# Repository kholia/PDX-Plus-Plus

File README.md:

#### PDX++ (PDX Plus Plus)

A port of https://github.com/WB2CBA/ADX/ to Raspberry Pi Pico with a couple of
enhancements.

PDX++ uses CD2003 (an AM receiver chip) for RX. For TX, we rely on the
AFSK-driving-Si5351 technique. PDX++ uses the common 3 x BS170 Class-E
amplifier design.

Bands covered: 80-meter to 10-meter.

Note: This repository contains the complete source-code for PDX++ (including
KiCad design files).

Update (17-November-2021): PCB V0.01 was sucessfully validated and is on air!

First QSO from PDX++:

QSOs from PDX++:

Note: This project was built using the following:

- KiCad 6.0.x

- https://github.com/earlephilhower/arduino-pico (v2.6.3)

Cost to build: < 1600 INR (around ~20 USD). Including all connectors + LPF.

RX power consumption is 45mA @ 12.0 volts (around 0.56 watt).

#### Schematic

See [the PDX++ schematic](./PDX++.pdf).

#### Build Tips

For the `PCB V0.01` board, build and test the TX section first.

#### Features

- Easy inbuilt and self-sufficient Si5351 calibration

- Inbuilt BCI (broadcast interference) filter

- New AFSK circuit using a LM393 comparator

- Full CAT support (which avoids VOX mode which can trigger false TX under many
  conditions)

- [Optional] Native FT8 decoding on the Pico (via AA1GD)

  - Use https://github.com/kholia/pico_ft8_xcvr firmware

- [Optional] Native spotting (reporting to PSKReporter.info) when using Pico W

  - https://github.com/kholia/SunshineFT8/

#### BOM Sources

International users can buy from Mouser and DigiKey.

Here are some local BOM sources I use:

- https://inkocean.in/ - CD2003 (Chinese clone which is known to work fine)

- https://rarecomponents.com/store/1002 - NXP 1N4148

- https://projectpoint.in/ - CDIL 7805, PJ307 Stereo Socket, winding wire, high quality passives

- https://www.evelta.com/l7805-positive-voltage-regulator-1-5a-5v/ (alternate)

- https://robu.in/product/si5351a-i2c-8-khz-160-mhz-clock-generator-breakout-board-module/

- https://robu.in/product/raspberry-pi-pico/

- https://www.semikart.com/ - has everything we need and more

#### Credits

- https://github.com/WB2CBA/ADX/

- https://github.com/lu7did/ADX-rp2040

- https://github.com/lu7did (ZCD code, freqPIO code)

- https://github.com/aa1gd/pico_ft8_xcvr (AA1GD, for native FT8 decoding)

- https://www.qrz.com/DB/VU2BGS (layout and general help)

#### References

- https://f5npv.wordpress.com/homebrew-ft8qrp-afp-fsk-trx/

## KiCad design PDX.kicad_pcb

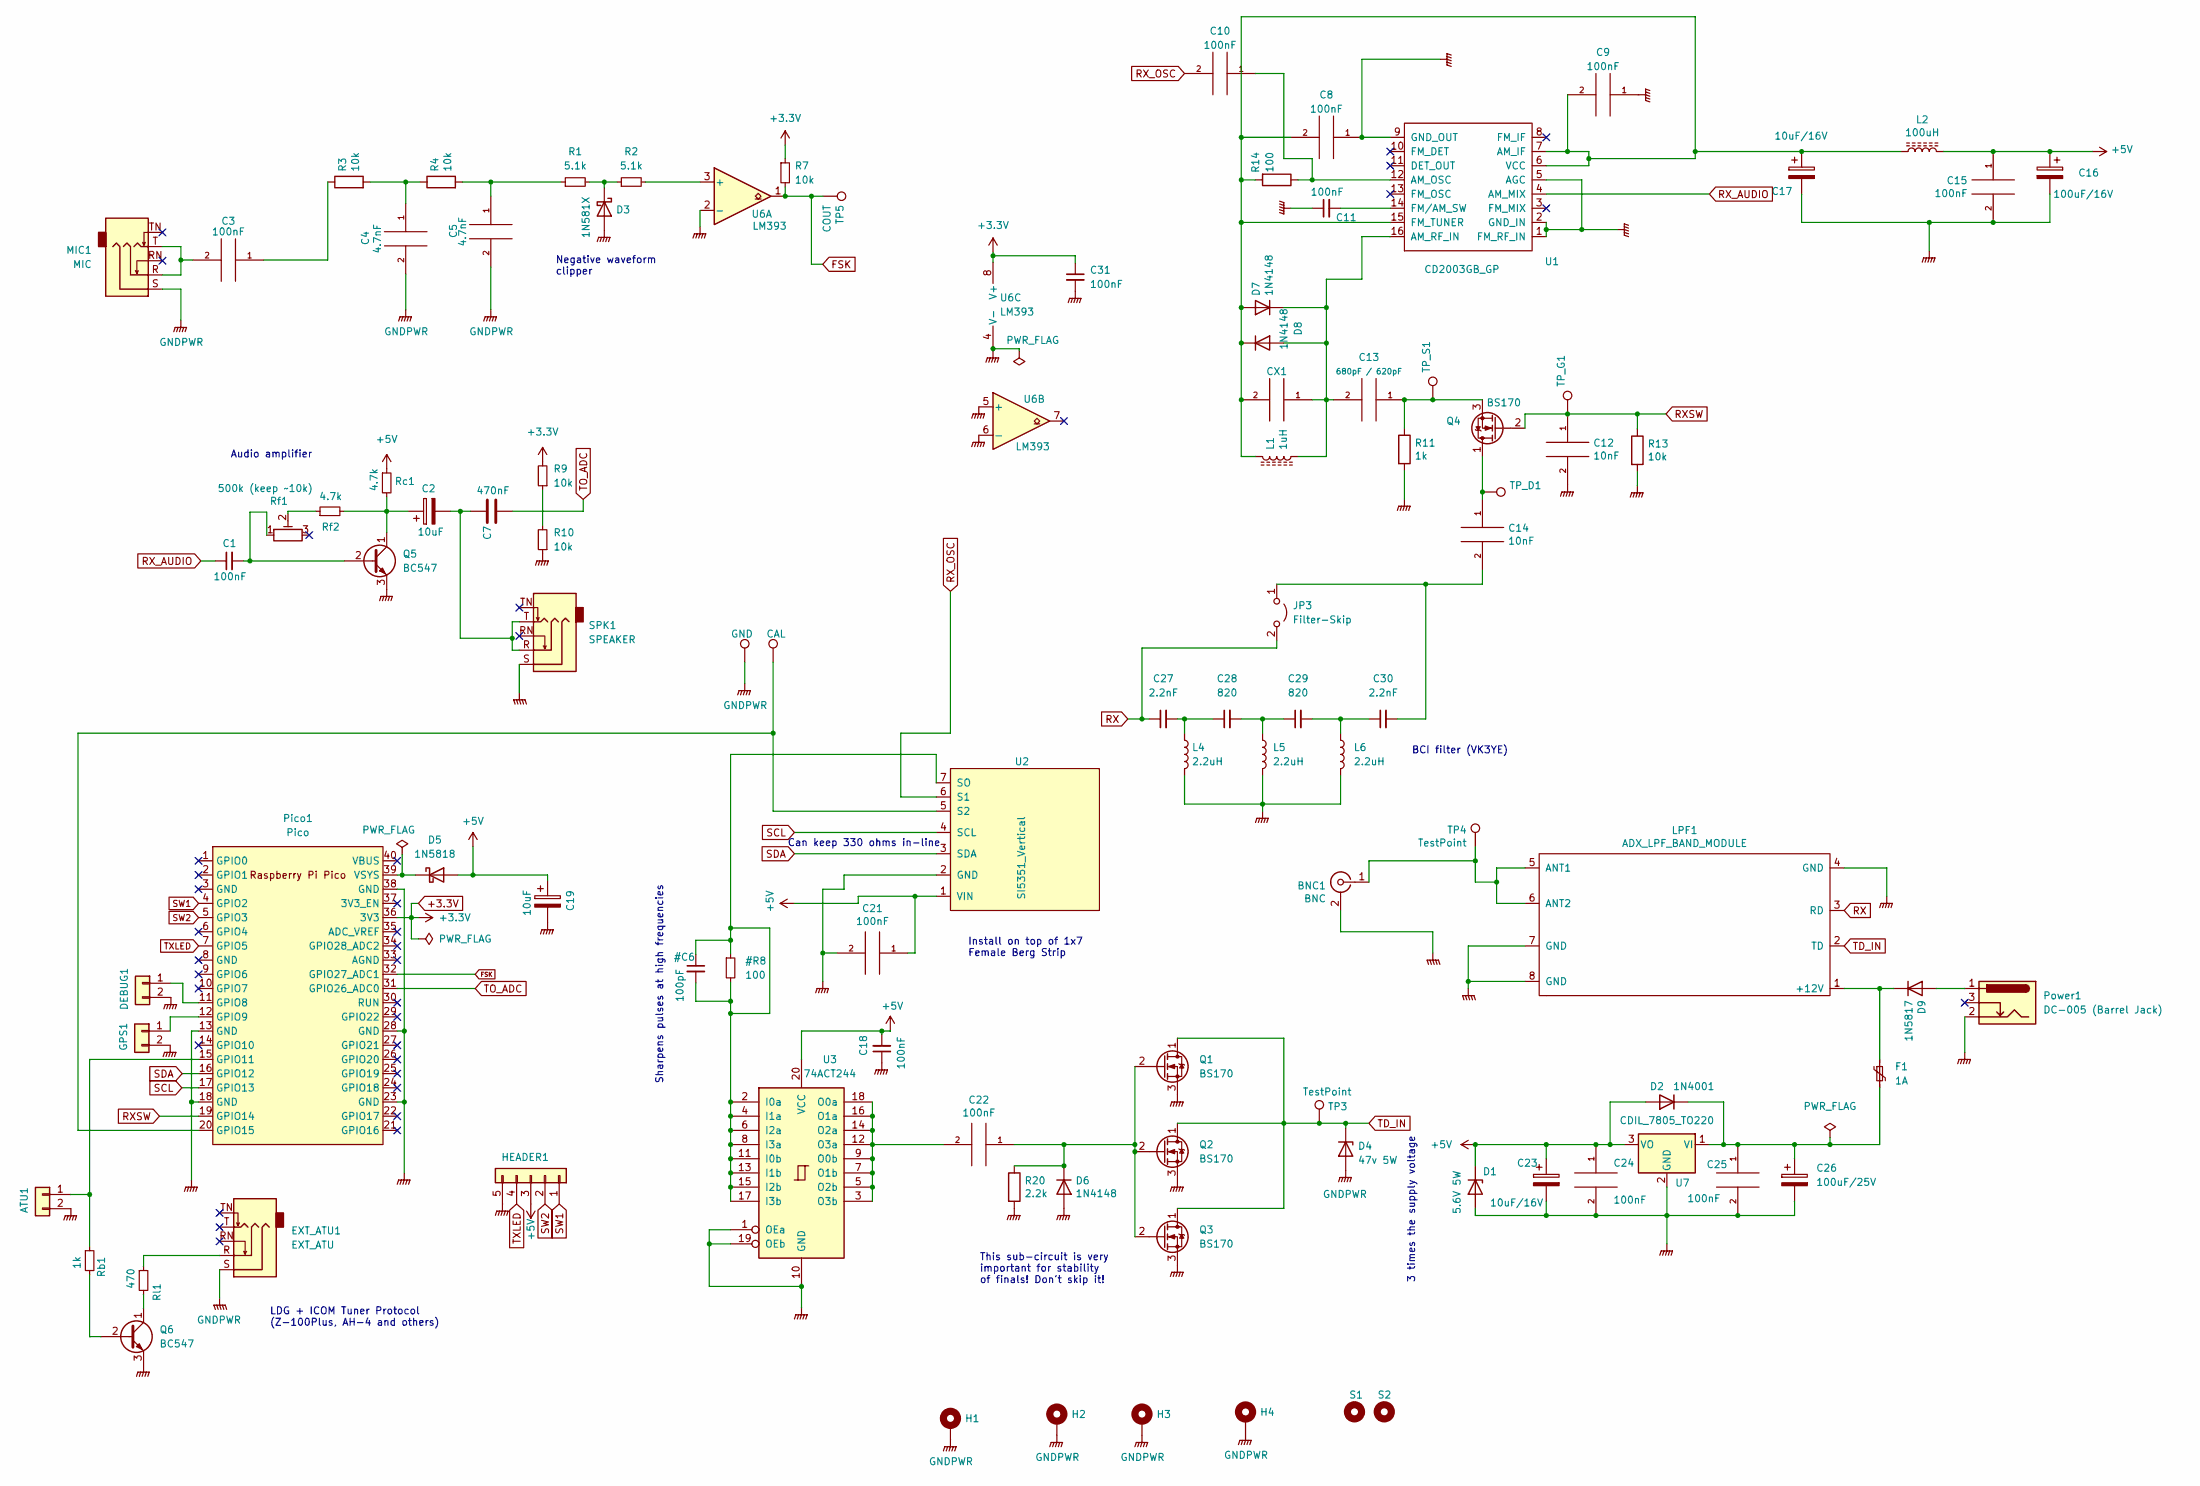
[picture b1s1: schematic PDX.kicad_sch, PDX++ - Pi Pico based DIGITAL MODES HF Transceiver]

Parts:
ATU1: Conn_01x02; PinHeader_1x02_P2.54mm_Vertical
BNC1: BNC; BNC_Amphenol_B6252HB-NPP3G-50_Horizontal
C1, C3, C8, C9, C10, C11, C15, C18, C21, C22: 100nF; C_Disc_D3.0mm_W1.6mm_P2.50mm
C2, C19: 10uF; CP_Radial_D5.0mm_P2.50mm
C4, C5: 4.7nF; C_Disc_D3.0mm_W1.6mm_P2.50mm
C7: 470nF; C_Disc_D3.0mm_W2.0mm_P2.50mm
C12, C14: 10nF; C_Disc_D3.0mm_W2.0mm_P2.50mm
C13: 680pF / 620pF; C_Disc_D3.0mm_W1.6mm_P2.50mm
C16: 100uF/16V; CP_Radial_D5.0mm_P2.50mm
C17: 10uF/16V; CP_Radial_D5.0mm_P2.50mm
C23: 10uF/16V; CP_Radial_D4.0mm_P2.00mm
C24, C25, C31: 100nF; C_Disc_D3.0mm_W2.0mm_P2.50mm
C26: 100uF/25V; CP_Radial_D4.0mm_P2.00mm
C27, C30: 2.2nF; C_Disc_D3.0mm_W1.6mm_P2.50mm
C28, C29: 820; C_Disc_D3.0mm_W1.6mm_P2.50mm
CX1: C_Disc_D3.0mm_W1.6mm_P2.50mm
D1: 5.6V 5W; D_DO-15_P5.08mm_Vertical_KathodeUp
D2: 1N4001; D_DO-41_SOD81_P2.54mm_Vertical_KathodeUp
D3: 1N581X; D_DO-41_SOD81_P2.54mm_Vertical_KathodeUp
D4: 47v 5W; D_DO-201_P3.81mm_Vertical_KathodeUp
D5: 1N5818; D_DO-41_SOD81_P2.54mm_Vertical_KathodeUp
D6, D7, D8: 1N4148; D_DO-35_SOD27_P2.54mm_Vertical_KathodeUp
D9: 1N5817; D_DO-41_SOD81_P2.54mm_Vertical_KathodeUp
DEBUG1: Conn_01x02; PinHeader_1x02_P2.54mm_Vertical
EXT_ATU1: EXT_ATU; PJ-307_Modded
F1: 1A; Fuse_BelFuse_0ZRE0005FF_L8.3mm_W3.8mm
GPS1: Conn_01x02; PinHeader_1x02_P2.54mm_Vertical
H1, H2, H3, H4: MountingHole_Pad; MountingHole_3.2mm_M3_ISO7380_Pad
HEADER1: Conn_01x05; PinHeader_1x05_P2.54mm_Vertical
JP3: Filter-Skip; PinHeader_1x02_P2.54mm_Vertical
L1: 1uH; L_Axial_L5.3mm_D2.2mm_P2.54mm_Vertical_Vishay_IM-1
L2: 100uH; R_Axial_DIN0204_L3.6mm_D1.6mm_P2.54mm_Vertical
L4, L5, L6: 2.2uH; L_Axial_L5.3mm_D2.2mm_P2.54mm_Vertical_Vishay_IM-1
LPF1: ADX_LPF_BAND_MODULE; uSDX_LPF_Band_Module
MIC1: MIC; PJ-307_Modded
Pico1: Pico; RPi_Pico_SMD_TH
Power1: DC-005 (Barrel Jack); XKB_DC-005-5A-2.0
Q1, Q2, Q3: BS170; PinSocket_1x03_P2.54mm_Vertical
Q4: BS170; TO-92_HandSolder
Q5, Q6: BC547; TO-92_HandSolder
R1, R2: 5.1k; R_Axial_DIN0204_L3.6mm_D1.6mm_P1.90mm_Vertical
R3, R4, R7, R9, R10, R13: 10k; R_Axial_DIN0204_L3.6mm_D1.6mm_P1.90mm_Vertical
R11: 1k; R_Axial_DIN0204_L3.6mm_D1.6mm_P1.90mm_Vertical
R14: 100; R_Axial_DIN0204_L3.6mm_D1.6mm_P1.90mm_Vertical
R20: 2.2k; R_Axial_DIN0204_L3.6mm_D1.6mm_P1.90mm_Vertical
Rb1: 1k; R_Axial_DIN0204_L3.6mm_D1.6mm_P1.90mm_Vertical
Rc1: 4.7k; R_Axial_DIN0204_L3.6mm_D1.6mm_P1.90mm_Vertical
Rf1: 500k (keep ~10k); Potentiometer_Runtron_RM-065_Vertical
Rf2: 4.7k; R_Axial_DIN0204_L3.6mm_D1.6mm_P1.90mm_Vertical
Rl1: 470; R_Axial_DIN0204_L3.6mm_D1.6mm_P1.90mm_Vertical
S1, S2: MountingHole; MountingHole_2.2mm_M2
SPK1: SPEAKER; PJ-307_Modded
TP3, TP4: TestPoint; TestPoint_THTPad_2.0x2.0mm_Drill1.0mm
TP5: COUT; TestPoint_THTPad_2.0x2.0mm_Drill1.0mm
TP7: GND; TestPoint_THTPad_2.0x2.0mm_Drill1.0mm
TP8: CAL; TestPoint_THTPad_2.0x2.0mm_Drill1.0mm
TP_D1: TestPoint_THTPad_1.0x1.0mm_Drill0.5mm
TP_G1: TestPoint_THTPad_1.0x1.0mm_Drill0.5mm
TP_S1: TestPoint_THTPad_1.0x1.0mm_Drill0.5mm
U1: CD2003GB_GP; DIP-16_W7.62mm_Socket
U2: SI5351_Vertical; SI5351 Module_Vertical
U3: 74ACT244; DIP-20_W7.62mm_LongPads
U6: LM393; DIP-8_W7.62mm
U7: CDIL_7805_TO220; TO-220-3_Vertical

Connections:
+3.3V: C31.1, Pico1.36 (3V3), R7.1, R9.2, U6.8 (V+)
+5V: C15.1, C16.1, C18.2, C19.1, C21.1, C23.1, C24.1, D1.1 (K), D2.2 (A), D5.2 (A), HEADER1.3, L2.1, Rc1.1, U2.1 (VIN), U3.20 (VCC), U7.3 (VO)
FSK: Pico1.32 (GPIO27_ADC1), R7.2, TP5.1, U6.1
GNDPWR: ATU1.2, BNC1.2 (Ext), C4.2, C5.2, C8.1, C9.1, C11.1, C12.2, C15.2, C16.2, C17.2, C18.1, C19.2, C21.2, C23.2, C24.2, C25.2, C26.2, C31.2, D1.2 (A), D3.2 (A), D4.2 (A), D6.2 (A), DEBUG1.2, EXT_ATU1.S, GPS1.2, H1.1, H2.1, H3.1, H4.1, HEADER1.5, L4.2, L5.2, L6.2, LPF1.4 (GND), LPF1.7 (GND), LPF1.8 (GND), MIC1.S, Pico1.13 (GND), Pico1.18 (GND), Pico1.23 (GND), Pico1.28 (GND), Pico1.38 (GND), Power1.2, Q1.3 (S), Q2.3 (S), Q3.3 (S), Q5.3 (E), Q6.3 (E), R10.1, R11.2, R13.2, R20.2, SPK1.S, TP7.1, U1.1 (FM_RF_IN), U1.2 (GND_IN), U1.5 (AGC), U1.9 (GND_OUT), U2.2 (GND), U3.1 (OEa), U3.10 (GND), U3.19 (OEb), U6.2 (-), U6.4 (V-), U6.5 (+), U6.6 (-), U7.2 (GND)
unnamed: ATU1.1, Pico1.15 (GPIO11), Rb1.1
unnamed: BNC1.1 (In), LPF1.5 (ANT1), LPF1.6 (ANT2), TP4.1
unnamed: C1.2, Q5.2 (B), Rf1.1
unnamed: C2.1, Q5.1 (C), Rc1.2, Rf2.2
unnamed: C2.2, C7.2, SPK1.R, SPK1.T
unnamed: C3.1, R3.1
unnamed: C3.2, MIC1.R, MIC1.T
unnamed: C4.1, R3.2, R4.1
unnamed: C5.1, R1.1, R4.2
unnamed: C10.1, R14.1, U1.12 (AM_OSC)
unnamed: C11.2, U1.14 (FM/AM_SW)
unnamed: C13.1, Q4.3 (S), R11.1, TP_S1.1
unnamed: C13.2, CX1.1, D7.1 (K), D8.2 (A), L1.1, U1.16 (AM_RF_IN)
unnamed: C14.1, Q4.1 (D), TP_D1.1
unnamed: C14.2, C30.2, JP3.1 (A)
unnamed: C8.2, C9.2, C17.1, CX1.2, D7.2 (A), D8.1 (K), L1.2, L2.2, R14.2, U1.6 (VCC), U1.7 (AM_IF), U1.15 (FM_TUNER)
unnamed: C22.1, D6.1 (K), Q1.2 (G), Q2.2 (G), Q3.2 (G), R20.1
unnamed: C22.2, U3.3 (O3b), U3.5 (O2b), U3.7 (O1b), U3.9 (O0b), U3.12 (O3a), U3.14 (O2a), U3.16 (O1a), U3.18 (O0a)
unnamed: C25.1, C26.1, D2.1 (K), F1.2, U7.1 (VI)
unnamed: C27.2, C28.1, L4.1
unnamed: C28.2, C29.1, L5.1
unnamed: C29.2, C30.1, L6.1
unnamed: D3.1 (K), R1.2, R2.1
unnamed: D5.1 (K), Pico1.39 (VSYS)
unnamed: D9.1 (K), F1.1, LPF1.1 (+12V)
unnamed: D9.2 (A), Power1.1
unnamed: DEBUG1.1, Pico1.11 (GPIO8)
unnamed: EXT_ATU1.R, Rl1.1
unnamed: GPS1.1, Pico1.12 (GPIO9)
unnamed: Pico1.20 (GPIO15), TP8.1, U2.5 (S2)
unnamed: Q6.1 (C), Rl1.2
unnamed: Q6.2 (B), Rb1.2
unnamed: R2.2, U6.3 (+)
unnamed: R9.1, R10.2
unnamed: Rf1.2, Rf2.1
unnamed: U2.7 (SO), U3.2 (I0a), U3.4 (I1a), U3.6 (I2a), U3.8 (I3a), U3.11 (I0b), U3.13 (I1b), U3.15 (I2b), U3.17 (I3b)
RX: C27.1, JP3.2 (B), LPF1.3 (RD)
RXSW: C12.1, Pico1.19 (GPIO14), Q4.2 (G), R13.1, TP_G1.1
RX_AUDIO: C1.1, U1.4 (AM_MIX)
RX_OSC: C10.2, U2.6 (S1)
SCL: Pico1.17 (GPIO13), U2.4 (SCL)
SDA: Pico1.16 (GPIO12), U2.3 (SDA)
SW1: HEADER1.1, Pico1.4 (GPIO2)
SW2: HEADER1.2, Pico1.5 (GPIO3)
TD_IN: D4.1 (K), LPF1.2 (TD), Q1.1 (D), Q2.1 (D), Q3.1 (D), TP3.1
TO_ADC: C7.1, Pico1.31 (GPIO26_ADC0)
TXLED: HEADER1.4, Pico1.7 (GPIO5)

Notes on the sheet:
Install on top of 1x7 Female Berg Strip
This sub-circuit is very important for stability of finals! Don't skip it!
Audio amplifier
Can keep 330 ohms in-line
Sharpens pulses at high frequencies
Negative waveform clipper
LDG + ICOM Tuner Protocol (Z-100Plus, AH-4 and others)
BCI filter (VK3YE)
3 times the supply voltage

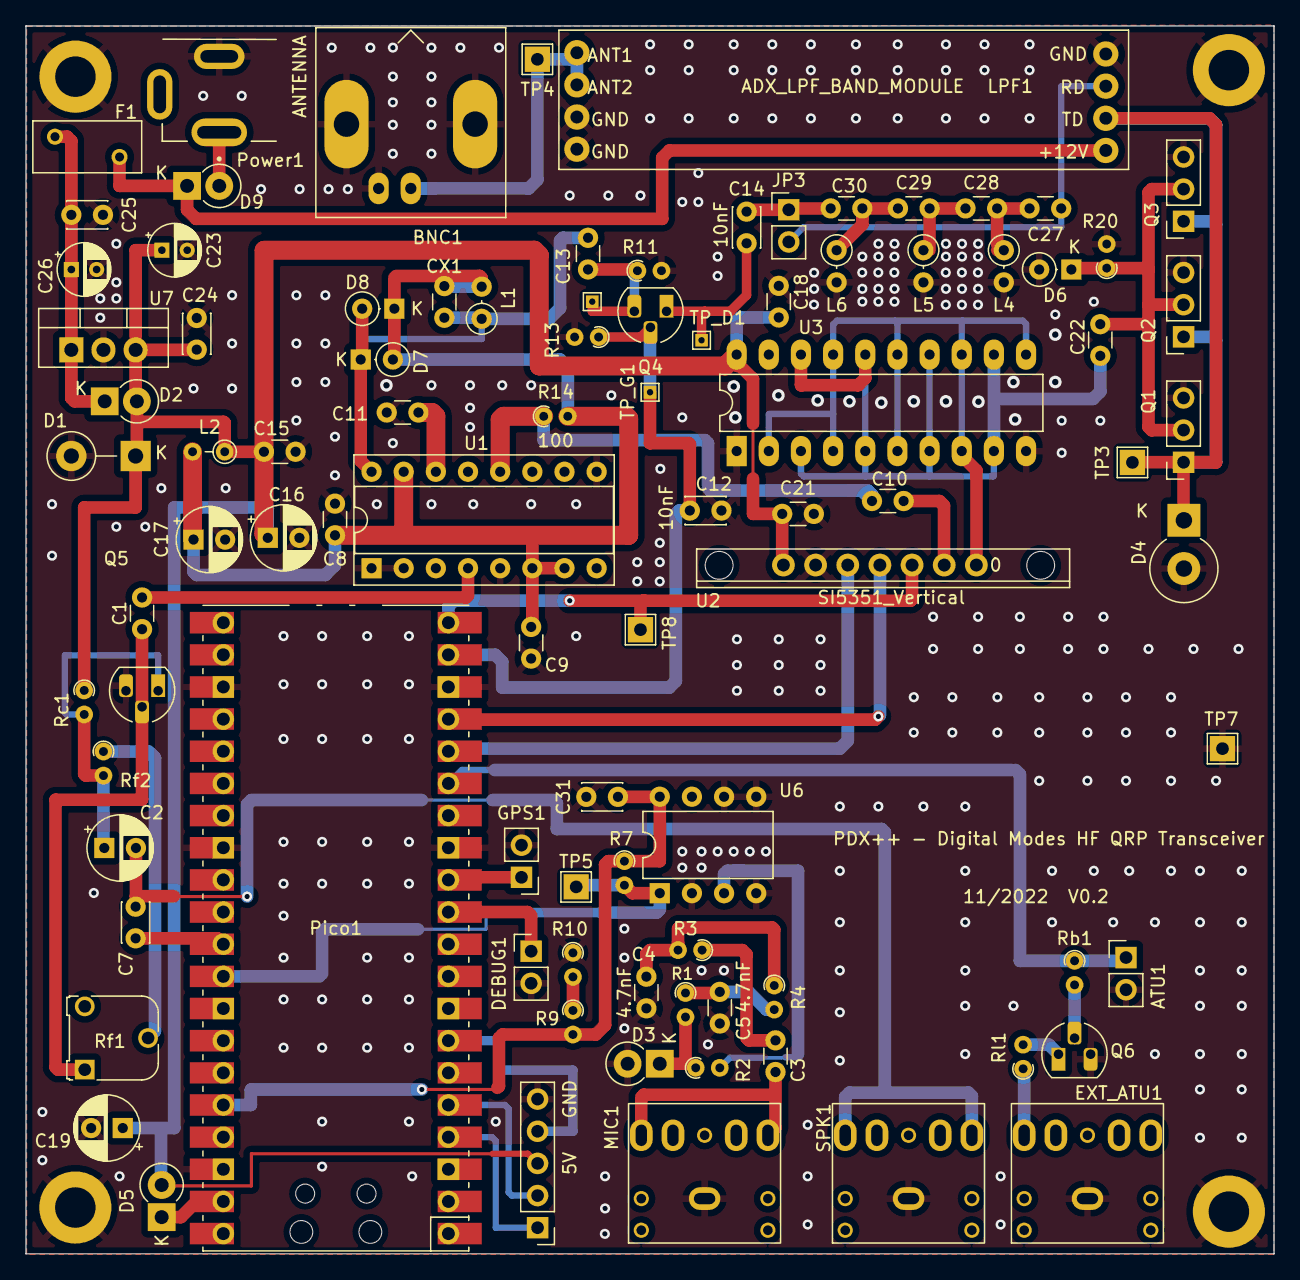
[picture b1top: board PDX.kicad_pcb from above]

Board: 2 copper layers, 98.6 x 97.0 mm, 98 parts (0 on the bottom side), 51 nets.

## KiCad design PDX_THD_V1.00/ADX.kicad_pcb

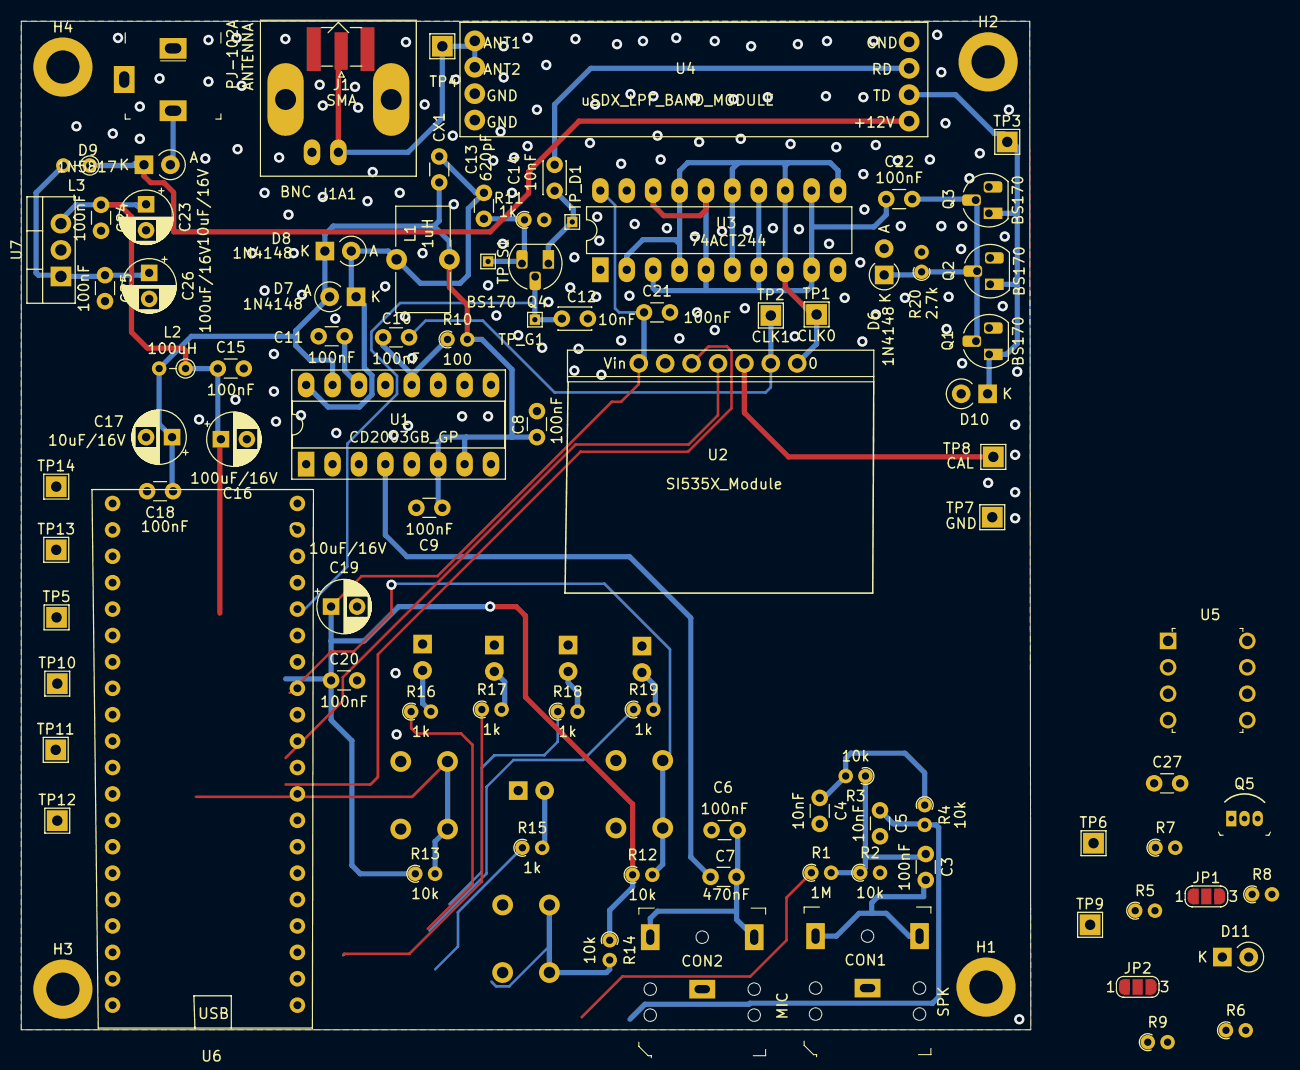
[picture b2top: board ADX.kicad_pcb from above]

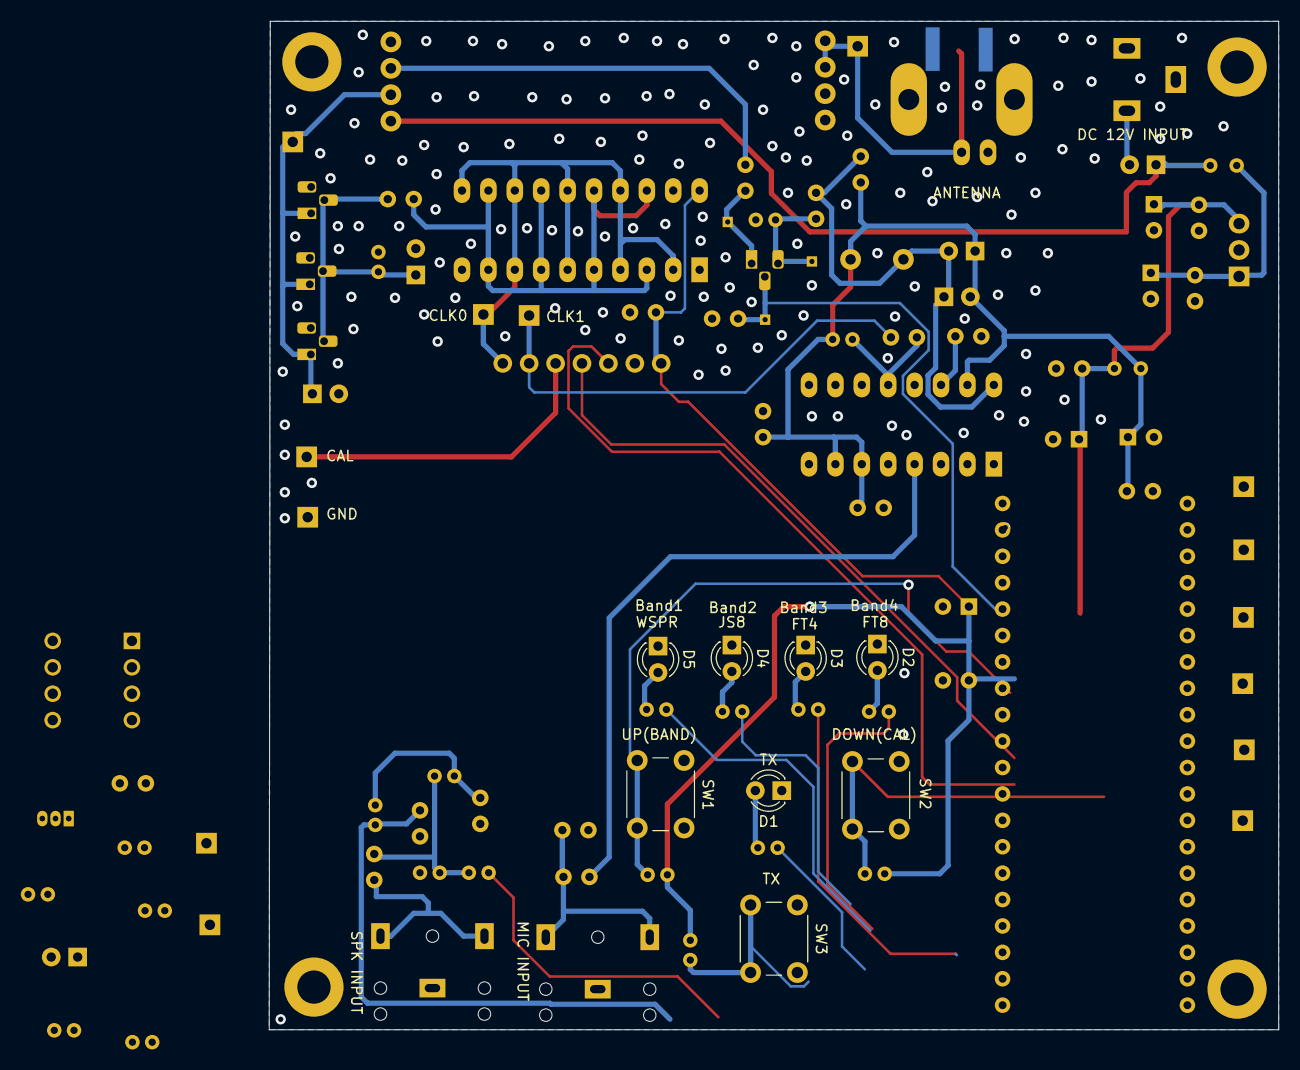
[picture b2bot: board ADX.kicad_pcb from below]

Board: 2 copper layers, 97.1 x 97.0 mm, 103 parts (8 on the bottom side), 53 nets.

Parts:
C3, C6, C8, C9, C10, C11, C15, C18, C20, C21, C22, C24, C25, C27: 100nF; C_Disc_D3.0mm_W1.6mm_P2.50mm
C4, C5: 10nF; C_Disc_D3.0mm_W1.6mm_P2.50mm
C7: 470nF; C_Disc_D3.0mm_W1.6mm_P2.50mm
C12, C14: 10nF; C_Disc_D3.0mm_W2.0mm_P2.50mm
C13: 620pF; C_Disc_D3.0mm_W1.6mm_P2.50mm
C16, C26: 100uF/16V; CP_Radial_D5.0mm_P2.50mm
C17, C19, C23: 10uF/16V; CP_Radial_D5.0mm_P2.50mm
CON1: SPK; Headphone_Jack_3.5mm_SJ1-3523N
CON2: MIC; Headphone_Jack_3.5mm_SJ1-3523N
CX1: C_Disc_D3.0mm_W1.6mm_P2.50mm
D1: TX; LED_D3.0mm
D2: FT8; LED_D3.0mm
D3: FT4; LED_D3.0mm
D4: JS8; LED_D3.0mm
D5: WSPR; LED_D3.0mm
D6: 1N4148; D_A-405_P2.54mm_Vertical_AnodeUp
D7, D8: 1N4148; D_A-405_P2.54mm_Vertical_KathodeUp
D9: 1N5817; D_A-405_P2.54mm_Vertical_KathodeUp
D10: 1N4756; D_A-405_P2.54mm_Vertical_KathodeUp
D11: 1N34; D_A-405_P2.54mm_Vertical_KathodeUp
H1, H2, H3, H4: MountingHole_Pad; MountingHole_3.2mm_M3_ISO7380_Pad
J1: SMA; SMA_Samtec_SMA-J-P-X-ST-EM1_EdgeMount
J1A1: BNC; BNC_Amphenol_B6252HB-NPP3G-50_Horizontal
J2: PJ-102A; Barrel_Jack_5.5mmODx2.1mmID_PJ-102A
JP1: T_O SLCT1; SolderJumper-3_P1.3mm_Open_RoundedPad1.0x1.5mm_NumberLabels
JP2: T_O SLCT2; SolderJumper-3_P1.3mm_Open_RoundedPad1.0x1.5mm_NumberLabels
L1: 1uH; L_Toroid_Vertical_L10.0mm_W5.0mm_P5.08mm
L2, L3: 100uH; R_Axial_DIN0204_L3.6mm_D1.6mm_P2.54mm_Vertical
Q1, Q2, Q3: BS170; TO-92_HandSolder
Q4: BS170; TO-92L_HandSolder
Q5: BS170; TO-92-3
R1: 1M; R_Axial_DIN0204_L3.6mm_D1.6mm_P1.90mm_Vertical
R2, R3, R4, R7, R12, R13, R14: 10k; R_Axial_DIN0204_L3.6mm_D1.6mm_P1.90mm_Vertical
R5, R6, R8, R11, R15, R16, R17, R18, R19: 1k; R_Axial_DIN0204_L3.6mm_D1.6mm_P1.90mm_Vertical
R9: 100k; R_Axial_DIN0204_L3.6mm_D1.6mm_P1.90mm_Vertical
R10: 100; R_Axial_DIN0204_L3.6mm_D1.6mm_P1.90mm_Vertical
R20: 2.7k; R_Axial_DIN0204_L3.6mm_D1.6mm_P1.90mm_Vertical
SW1: UP(BAND); SW_PUSH_6mm
SW2: DOWN(CAL); SW_PUSH_6mm
SW3: TX; SW_PUSH_6mm
TP1: CLK0; TestPoint_THTPad_2.0x2.0mm_Drill1.0mm
TP2: CLK1; TestPoint_THTPad_2.0x2.0mm_Drill1.0mm
TP3, TP4: TestPoint; TestPoint_THTPad_2.0x2.0mm_Drill1.0mm
TP5: ATU; TestPoint_THTPad_2.0x2.0mm_Drill1.0mm
TP6, TP12: CW; TestPoint_THTPad_2.0x2.0mm_Drill1.0mm
TP7: GND; TestPoint_THTPad_2.0x2.0mm_Drill1.0mm
TP8: CAL; TestPoint_THTPad_2.0x2.0mm_Drill1.0mm
TP9: AF; TestPoint_THTPad_2.0x2.0mm_Drill1.0mm
TP10: BT; TestPoint_THTPad_2.0x2.0mm_Drill1.0mm
TP11: CLK; TestPoint_THTPad_2.0x2.0mm_Drill1.0mm
TP13: UART_RX; TestPoint_THTPad_2.0x2.0mm_Drill1.0mm
TP14: UART_TX; TestPoint_THTPad_2.0x2.0mm_Drill1.0mm
TP_D1: TestPoint_THTPad_1.0x1.0mm_Drill0.5mm
TP_G1: TestPoint_THTPad_1.0x1.0mm_Drill0.5mm
TP_S1: TestPoint_THTPad_1.0x1.0mm_Drill0.5mm
U1: CD2003GB_GP; DIP-16_W7.62mm_Socket_LongPads
U2: SI535X_Module; SI5351 Module_Vertical
U3: 74ACT244; DIP-20_W7.62mm_LongPads
U4: uSDX_LPF_BAND_MODULE; uSDX_LPF_Band_Module
U5: LM393N_LTB; DIP-8_W7.62mm
U6: RP2040_PICO; RPI_PICO
U7: LM7805; TO-220-3_Vertical

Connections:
+3.3V: C27.2, R1.1, R7.1, R8.1, U5.8, U6.36
+5V: C15.1, C16.1, C19.1, C20.1, C21.1, C23.1, C24.1, L2.1, R12.1, R13.1, R14.1, U2.1, U3.20, U6.40, U7.3
CAL: TP8.1, U2.5, U6.12
FSK: JP2.2, U6.32
FT4LED: R17.1, U6.7
FT8LED: R16.1, U6.6
GNDPWR: C4.2, C5.2, C6.2, C8.1, C9.1, C11.1, C12.2, C15.2, C16.2, C17.2, C18.2, C19.2, C20.2, C21.2, C23.2, C24.2, C25.2, C26.2, C27.1, CON1.1, CON2.1, D1.1, D2.1, D3.1, D4.1, D5.1, D6.2, D10.2, D11.1, H1.1, H2.1, H3.1, H4.1, J1.2, J1A1.2, J2.2, Q1.3, Q2.3, Q3.3, Q5.3, R2.2, R9.2, R11.2, R20.2, SW1.1, SW2.1, SW3.1, TP7.1, U1.1, U1.2, U1.5, U1.9, U2.2, U3.1, U3.10, U3.19, U4.4, U4.7, U4.8, U5.3, U5.4, U6.3, U6.8, U6.13, U6.18, U6.23, U6.28, U6.33, U6.38, U7.2
JS8LED: R18.1, U6.9
unnamed: C3.1, R1.2, R2.1, R3.1
unnamed: C3.2, CON1.3, TP9.1
unnamed: C4.1, R3.2, R4.1
unnamed: C5.1, JP1.2, R4.2
unnamed: C6.1, C7.1, CON2.2, CON2.3
unnamed: C10.1, R10.1
unnamed: C11.2, U1.16
unnamed: C13.1, Q4.3, R11.1, TP_S1.1, U1.6, U1.7, U1.15
unnamed: C13.2, CX1.1, D7.1, D8.2, L1.1
unnamed: C14.1, Q4.1, TP_D1.1
unnamed: C8.2, C9.2, C17.1, C18.1, CX1.2, D7.2, D8.1, L1.2, L2.2, R10.2
unnamed: C22.1, D6.1, Q1.2, Q2.2, Q3.2, R20.1
unnamed: C22.2, U3.3, U3.5, U3.7, U3.9, U3.12, U3.14, U3.16, U3.18
unnamed: C25.1, C26.1, L3.2, U7.1
unnamed: CON1.2, TP6.1
unnamed: D1.2, R15.2
unnamed: D2.2, R16.2
unnamed: D3.2, R17.2
unnamed: D4.2, R18.2
unnamed: D5.2, R19.2
unnamed: D9.1, L3.1, U4.1
unnamed: D9.2, J2.1
unnamed: D11.2, R5.1, R6.2
unnamed: J1.1, J1A1.1, TP4.1, U4.5, U4.6
unnamed: JP1.1, R5.2
unnamed: JP1.3, Q5.2, R9.1
unnamed: JP2.1, Q5.1, R8.2
unnamed: JP2.3, R7.2, U5.1
unnamed: R6.1, U5.2
unnamed: TP1.1, U2.7, U3.2, U3.4, U3.6, U3.8, U3.11, U3.13, U3.15, U3.17
unnamed: TP5.1, U6.20
unnamed: TP13.1, U6.16
unnamed: TP14.1, U6.17
RX: C14.2, U4.3
RXA: C7.2, U1.4
RXSW: C12.1, Q4.2, TP_G1.1, U6.4
RX_OSC: C10.2, TP2.1, U2.6
SCL: U2.4, U6.22
SDA: U2.3, U6.21
SW1: R12.2, SW1.2, TP10.1, U6.14
SW2: R13.2, SW2.2, TP11.1, U6.15
SW3: R14.2, SW3.2, TP12.1, U6.11
TD_IN: D10.1, Q1.1, Q2.1, Q3.1, TP3.1, U4.2
TXLED: R15.1, U6.5
WSPRLED: R19.1, U6.10

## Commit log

2022-12-01 PCB v0.2 + Initial firmware
    PCB changes:
    - Use `TO-92_HandSolder` footprint
    - Use (optional) sockets for BS170 finals!
    - Add `Test Point` for comparator output
    - Remove onboard heatsink - it is not needed
    - Provide +5V on the output header
